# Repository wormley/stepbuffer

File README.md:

KiCad File Formats

This is a Step Stick style adapter with a level shifter/buffer
to allow boards with low current and/or 3.3v outputs to feed
off-board drivers.

It takes step+direction+enable inputs and outputs them 
non-inverted on the motor pins, along with ground.

The jumper block allows driving the buffer from Vio, Vmot or remove the 
jumper and feed with a 2 pin female from another +5v source.

If Vio is 5v then you can use that. If it's 3.3v then output will also
be 3.3v, but this can work if you just need more current.

If your board allows Vmot to be 5v(thus is only used for the stepper
drivers) then you can use Vmot. 

Else connect +5v and ground if needed to the header pins.

The Buffer Chip:
http://www.ti.com/product/SN74LV4T125/technicaldocuments

The schematic has a polarized capacitor just in case someone wants 
to use one. A standard MLCC is fine.

The 6 pin header can be left out and a 2 pin header used if externally
powered. Or hard wire the holes for desired power.

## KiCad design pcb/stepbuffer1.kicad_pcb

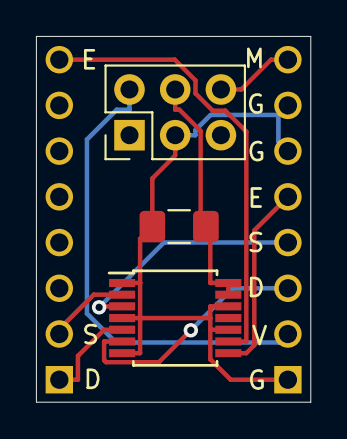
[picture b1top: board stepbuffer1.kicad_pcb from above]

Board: 2 copper layers, 15.2 x 20.3 mm, 5 parts (0 on the bottom side), 10 nets.

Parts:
C1: CP; C_1206_3216Metric_Pad1.42x1.75mm_HandSolder
J1: Conn_02x03_Odd_Even; PinHeader_2x03_P2.54mm_Vertical
P1, P2: MA08-1; 1X08-S
U1: SN74LV4T125; TSSOP-14_4.4x5mm_P0.65mm

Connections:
/+VM: J1.6, P2.8
/BMA1: P2.5, U1.8
/BMB1: P2.4, U1.3
/BMB2: P2.3, U1.6
/DIR: P1.1, U1.5
/EN: P1.8, U1.9
/STEP: P1.2, U1.2
/VCC_IO: J1.2, P2.2
GND: C1.2, J1.3, P2.1, P2.6, P2.7, U1.1, U1.4, U1.7, U1.10, U1.12
unnamed: C1.1, J1.4, U1.13, U1.14

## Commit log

2020-01-16 First
2020-01-16 Initial documentation
2020-01-21 Update documentation
2020-01-21 Add schematic PNG
2020-05-02 Add all additional files Add additional board prototype for a plug-in to screw terminal board
